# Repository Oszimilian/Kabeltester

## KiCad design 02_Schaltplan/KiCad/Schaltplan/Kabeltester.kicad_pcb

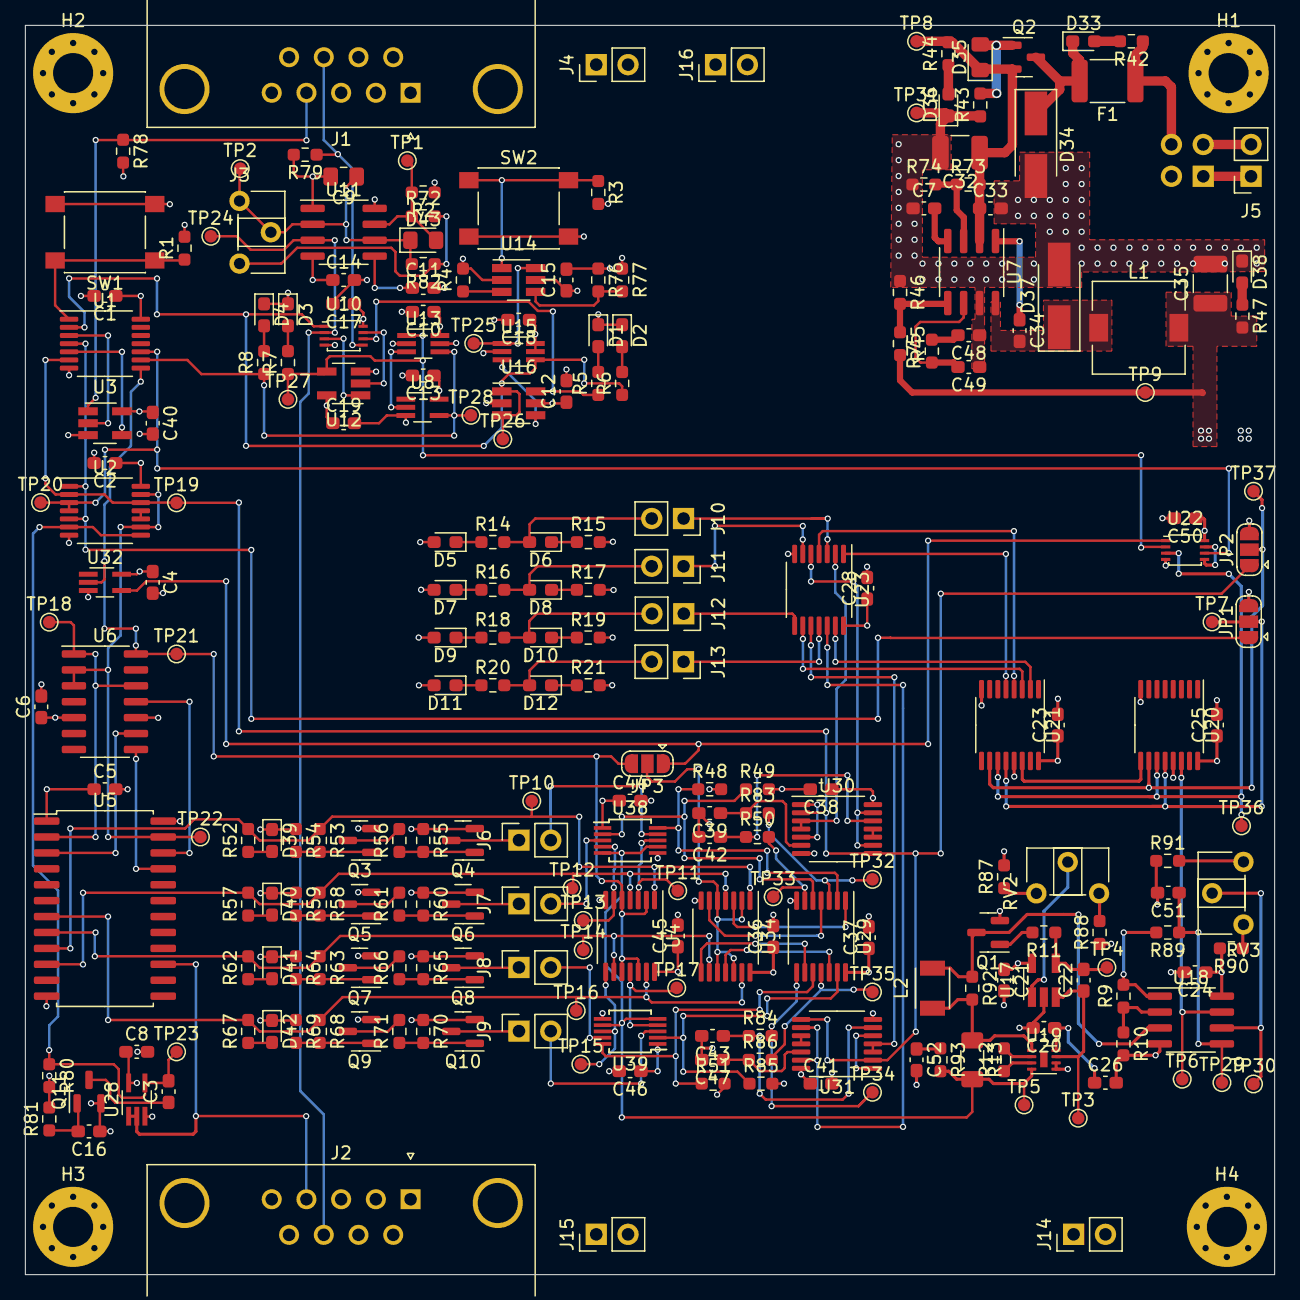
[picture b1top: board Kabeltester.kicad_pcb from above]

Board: 4 copper layers, 99.7 x 99.7 mm, 253 parts (1 on the bottom side), 160 nets.

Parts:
C1, C2, C3, C4, C5, C6, C8, C10, C11, C12, C13, C14, C15, C17, C18, C19, C20, C21, C23, C24, C25, C26, C28, C34, C36, C37, C38, C40, C41, C44, C45, C46, C50, C51: 100nF; C_0603_1608Metric_Pad1.08x0.95mm_HandSolder
C7: 10pF; C_0603_1608Metric_Pad1.08x0.95mm_HandSolder
C9: 3,9uF; C_0805_2012Metric_Pad1.18x1.45mm_HandSolder
C16: 1uF; C_0603_1608Metric_Pad1.08x0.95mm_HandSolder
C22: 1nF; C_0603_1608Metric_Pad1.08x0.95mm_HandSolder
C32: 22uF; C_1210_3225Metric_Pad1.33x2.70mm_HandSolder
C33, C52: 10nF; C_0603_1608Metric_Pad1.08x0.95mm_HandSolder
C35: 100uF; C_1210_3225Metric_Pad1.33x2.70mm_HandSolder
C39, C42, C43, C47: 470nF; C_0603_1608Metric_Pad1.08x0.95mm_HandSolder
C48: 2nF; C_0603_1608Metric_Pad1.08x0.95mm_HandSolder
C49: 8,2nF; C_0603_1608Metric_Pad1.08x0.95mm_HandSolder
D1, D5, D7, D9, D11, D33: LED/ROT; LED_0603_1608Metric_Pad1.05x0.95mm_HandSolder
D2, D6, D8, D10, D12, D36, D38: LED/GRUEN; LED_0603_1608Metric_Pad1.05x0.95mm_HandSolder
D3, D4, D39, D40, D41, D42: LED/GELB; LED_0603_1608Metric_Pad1.05x0.95mm_HandSolder
D34: SMAJ10CA; D_SMA_Handsoldering
D35: BZX585-C5V1; D_0805_2012Metric_Pad1.15x1.40mm_HandSolder
D37: B340A; D_SMA_Handsoldering
D43: BAS416; D_0805_2012Metric_Pad1.15x1.40mm_HandSolder
F1: 100mA M; Fuse_1812_4532Metric_Pad1.30x3.40mm_HandSolder
H1, H2, H3, H4: MountingHole; MountingHole_3.2mm_M3_Pad_Via
J1: INPUT/MALE-DB9; DSUB-9_Male_Horizontal_P2.77x2.84mm_EdgePinOffset4.94mm_Hou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
J2: OUTPUT/FEMALE-DB9; DSUB-9_Female_Horizontal_P2.77x2.84mm_EdgePinOffset4.94mm_H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
J3: 5k Poti; Potentiometer_ACP_CA6-H2,5_Horizontal
J4: VCC; PinHeader_1x02_P2.54mm_Vertical
J5: 9V_Batt; PinSocket_1x02_P2.54mm_Vertical
J6, J7, J8, J9: MEASURE-CON; PinSocket_1x02_P2.54mm_Vertical
J10, J11, J12, J13: Conn_02x01; PinSocket_1x02_P2.54mm_Vertical
J14, J15, J16: GND; PinHeader_1x02_P2.54mm_Vertical
JP1, JP2, JP3: Jumper; SolderJumper-3_P1.3mm_Open_RoundedPad1.0x1.5mm
L1: 6,8uH; L_7.3x7.3_H4.5
L2: L; L_TDK_NLV32_3.2x2.5mm
Q1: SI2318; SOT-23
Q2, Q4, Q6, Q8, Q10: Si2301; SOT-23
Q3, Q5, Q7, Q9: BSS123; SOT-23
Q11: BC858; SOT-23
R1, R3, R43, R48, R49, R50, R51, R54, R55, R59, R60, R64, R65, R69, R70, R78, R79, R80, R81, R83, R84, R85, R86, R89: 10k; R_0603_1608Metric_Pad0.98x0.95mm_HandSolder
R2: 18k; R_0603_1608Metric_Pad0.98x0.95mm_HandSolder
R4: 820k; R_0603_1608Metric_Pad0.98x0.95mm_HandSolder
R5, R7, R8, R14, R16, R18, R20, R52, R57, R62, R67: 1k6; R_0603_1608Metric_Pad0.98x0.95mm_HandSolder
R6, R15, R17, R19, R21, R47: 1k2; R_0603_1608Metric_Pad0.98x0.95mm_HandSolder
R9, R56, R61, R66, R71, R90, R91: 0R; R_0603_1608Metric_Pad0.98x0.95mm_HandSolder
R10, R82: NP; R_0603_1608Metric_Pad0.98x0.95mm_HandSolder
R11: 1k8; R_0603_1608Metric_Pad0.98x0.95mm_HandSolder
R12, R87, R88: 1k; R_0603_1608Metric_Pad0.98x0.95mm_HandSolder
R13: 1R; R_1206_3216Metric_Pad1.30x1.75mm_HandSolder
R42: 3k9; R_0603_1608Metric_Pad0.98x0.95mm_HandSolder
R44: 3k3; R_0603_1608Metric_Pad0.98x0.95mm_HandSolder
R45: 10k2; R_0603_1608Metric_Pad0.98x0.95mm_HandSolder
R46: 1k96; R_0603_1608Metric_Pad0.98x0.95mm_HandSolder
R53, R58, R63, R68: 510R; R_0603_1608Metric_Pad0.98x0.95mm_HandSolder
R72: 15k; R_0603_1608Metric_Pad0.98x0.95mm_HandSolder
R73: 680k; R_0603_1608Metric_Pad0.98x0.95mm_HandSolder
R74: 150k; R_0603_1608Metric_Pad0.98x0.95mm_HandSolder
R75: 34k; R_0603_1608Metric_Pad0.98x0.95mm_HandSolder
R76: 560k; R_0603_1608Metric_Pad0.98x0.95mm_HandSolder
R77: 1M; R_0603_1608Metric_Pad0.98x0.95mm_HandSolder
R92: 22R; R_0603_1608Metric_Pad0.98x0.95mm_HandSolder
R93: ?; R_0603_1608Metric_Pad0.98x0.95mm_HandSolder
RV2, RV3: 20k; Potentiometer_ACP_CA6-H2,5_Horizontal
SW1: START; SW_Push_1P1T_NO_6x6mm_H9.5mm
SW2: MODE; SW_Push_1P1T_NO_6x6mm_H9.5mm
SW3: PWR ON/OFF; PinSocket_2x02_P2.54mm_Vertical
TP1, TP2, TP3, TP4, TP5, TP6, TP7, TP8, TP9, TP10, TP11, TP12, TP13, TP14, TP15, TP16, TP17, TP18, TP19, TP20, TP21, TP22, TP23, TP24, TP25, TP26, TP27, TP28, TP29, TP30, TP31, TP32, TP33, TP34, TP35, TP36, TP37: TestPoint; TestPoint_Pad_D1.0mm
U1, U4, U23, U34: 74HC08PW; TSSOP-14_4.4x5mm_P0.65mm
U2, U30, U31: 74HC02PW; TSSOP-14_4.4x5mm_P0.65mm
U3, U12: 74AHC1G32; SOT-23-5_HandSoldering
U5: CD74HC4514M96; SOIC-24W_7.5x15.4mm_P1.27mm
U6: SN74LS93; SOIC-14_3.9x8.7mm_P1.27mm
U7: TPS_54331; SOIC-8_3.9x4.9mm_P1.27mm
U8, U32: 74AHC1G14; SOT-353_SC-70-5_Handsoldering
U10, U22: 74AHC2G08; VSSOP-8_2.4x2.1mm_P0.5mm
U11: NE555; SOIC-8_3.9x4.9mm_P1.27mm
U13, U15: 74LVC1G175; SOT-363_SC-70-6_Handsoldering
U14: LTC6993; SOT-23-6_Handsoldering
U16: 74LVC2G14; SOT-23-6_Handsoldering
U17: LMV321AUIDBVR; SOT-23-5_HandSoldering
U18: LMV358MM; SOIC-8_3.9x4.9mm_P1.27mm
U19: INA826AIDRGT; DFN-8-1EP_2x2mm_P0.5mm_EP0.6x1.2mm
U20, U21: 74HC595; TSSOP-16_4.4x5mm_P0.65mm
U28: 74HC1G126; SOT-353_SC-70-5_Handsoldering
U29: 74HC86PW; TSSOP-14_4.4x5mm_P0.65mm
U38, U39: DG2535; MSOP-10_3x3mm_P0.5mm

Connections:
+5V: C1.1, C2.1, C4.1, C5.1, C6.1, C8.1, C10.1, C12.1, C13.1, C14.1, C15.1, C16.1, C17.1, C18.1, C19.1, C20.1, C21.1, C23.1, C24.1, C25.1, C26.1, C28.1, C35.1, C36.1, C37.1, C38.1, C40.1, C41.1, C44.1, C45.1, C46.1, C50.1, D5.2 (A), D7.2 (A), D9.2 (A), D11.2 (A), J1.1, J1.5, J2.1, J2.5, J4.1, J4.2, JP1.3 (B), JP2.3 (B), L1.2, Q4.2 (S), Q6.2 (S), Q8.2 (S), Q10.2 (S), Q11.2 (E), R2.1, R45.2, R47.2, R55.1, R60.1, R65.1, R70.1, R77.1, R87.2, R90.2, SW1.2, SW2.2, TP9.1, U1.14 (VCC), U2.14 (VCC), U3.5 (VCC), U4.14 (VCC), U5.1 (LE), U5.24 (VCC), U6.5 (VCC), U8.5 (VCC), U10.8 (VCC), U11.4 (RESET), U11.8 (VCC), U12.5 (VCC), U13.5 (VCC), U13.6 (MR), U14.5 (VCC), U15.5 (VCC), U15.6 (MR), U16.5 (VCC), U17.5 (V+), U18.8 (V+), U19.8 (+VS), U20.16 (VCC), U21.16 (VCC), U22.8 (VCC), U23.14 (VCC), U28.5 (VCC), U29.14 (VCC), U30.14 (VCC), U31.14 (VCC), U32.5 (VCC), U34.14 (VCC), U38.1 (V+), U39.1 (V+)
+9V: C32.1, C33.1, D35.1 (K), Q2.2 (S), R44.2, R73.2, TP8.1, U7.2 (VIN)
/Versorgung/PH: C34.2, D37.1 (K), L1.1, U7.8 (PH)
CC_Output: TP6.1, U18.7, U20.14 (SER)
CC_Voltage: L2.2, Q1.3 (D), R92.1, U18.3 (+)
DK_INPUT_1: R48.1, U29.2 (1B), U38.10 (NO2)
DK_INPUT_2: R49.1, U29.5 (2B), U38.2 (NO1)
DK_INPUT_3: R51.1, U29.10 (3B), U39.10 (NO2)
DK_INPUT_4: R85.1, U29.13 (4B), U39.2 (NO1)
DK_OUT_1: U23.2 (B), U30.3 (1B), U30.4 (2Y)
DK_OUT_2: U23.5 (B), U30.9 (3B), U30.13 (4Y)
DK_OUT_3: U23.10 (B), U31.3 (1B), U31.4 (2Y)
DK_OUT_4: U23.12 (B), U31.9 (3B), U31.13 (4Y)
GND: C1.2, C2.2, C4.2, C5.2, C6.2, C7.1, C8.2, C9.2, C10.2, C11.2, C12.2, C13.2, C14.2, C15.2, C17.2, C18.2, C19.2, C20.2, C21.2, C23.2, C24.2, C25.2, C26.2, C28.2, C32.2, C33.2, C35.2, C36.2, C37.2, C38.2, C39.2, C40.2, C41.2, C42.2, C43.2, C44.2, C45.2, C46.2, C47.2, C48.1, C49.1, C50.2, C51.2, C52.2, D1.1 (K), D2.1 (K), D3.1 (K), D4.1 (K), D34.2 (A2), D36.1 (K), D37.2 (A), D38.1 (K), D39.1 (K), D40.1 (K), D41.1 (K), D42.1 (K), J1.6, J1.9, J2.6, J2.9, J14.1, J14.2, J15.1, J15.2, J16.1, J16.2, Q1.2 (S), Q3.2 (S), Q5.2 (S), Q7.2 (S), Q9.2 (S), R1.2, R3.2, R4.2, R10.2, R15.2, R17.2, R19.2, R21.2, R43.1, R46.1, R48.2, R49.2, R51.2, R54.1, R59.1, R64.1, R69.1, R74.1, R76.1, R78.2, R79.2, R80.2, R81.2, R85.2, R88.1, R91.1, SW3.2, TP31.1, U1.7 (GND), U2.7 (GND), U3.3 (GND), U4.7 (GND), U5.12 (GND), U6.10 (GND), U7.7 (GND), U8.3 (GND), U10.4 (GND), U11.1 (GND), U12.3 (GND), U13.2 (GND), U14.2 (GND), U15.2 (GND), U16.2 (GND), U17.2 (V-), U18.4 (V-), U19.5 (+VS), U19.6 (Ref), U20.8 (GND), U20.13 (EN), U21.8 (GND), U21.13 (EN), U22.4 (GND), U23.7 (GND), U28.3 (GND), U29.7 (GND), U30.7 (GND), U31.7 (GND), U32.3 (GND), U34.7 (GND), U38.6 (GND), U39.6 (GND)
INPUT_MEASURE_GOON: J1.4, R78.1, U3.1 (1A)
KS_INPUT: R13.2, R93.2, TP5.1, U19.4 (V+), U38.5 (NC1), U38.7 (NC2), U39.5 (NC1), U39.7 (NC2)
KS_OUT_1: U21.5 (QF), U23.1 (A)
KS_OUT_2: U21.4 (QE), U23.4 (A)
KS_OUT_3: U21.3 (QD), U23.9 (A)
KS_OUT_4: U21.2 (QC), U23.13 (A)
MEASURE_START: U1.5 (B), U3.4 (1Y)
NE55_OUT: J2.8, TP24.1, U10.2 (1B), U11.3 (OUT)
unnamed: C3.1, Q11.3 (C)
unnamed: C7.2, U7.4 (SS)
unnamed: C9.1, D43.1 (K), J3.1, J3.2, R82.2, TP2.1, U11.2 (TRIG), U11.6 (THRES)
unnamed: C11.1, U11.5 (CONT)
unnamed: C16.2, Q11.1 (B), R81.1
unnamed: C22.1, TP3.1, U17.3 (-)
unnamed: C22.2, R11.1, TP4.1, U17.4
unnamed: C34.1, U7.1 (BOOT)
unnamed: C39.1, R83.1, U30.6 (2B)
unnamed: C42.1, R50.1, U30.12 (4B)
unnamed: C43.1, R84.1, U31.6 (2B)
unnamed: C47.1, R86.1, U31.12 (4B)
unnamed: C48.2, R75.2
unnamed: C49.2, R75.1, U7.6 (COMP)
unnamed: C51.1, R89.1, TP29.1, U18.5 (+)
unnamed: C52.1, R93.1
unnamed: D1.2 (A), R5.2
unnamed: D2.2 (A), R6.2
unnamed: D3.2 (A), R7.2
unnamed: D4.2 (A), R8.2
unnamed: D5.1 (K), R14.1
unnamed: D6.1 (K), R15.1
unnamed: D6.2 (A), J10.2, R14.2
unnamed: D7.1 (K), R16.1
unnamed: D8.1 (K), R17.1
unnamed: D8.2 (A), J11.2, R16.2
unnamed: D9.1 (K), R18.1
unnamed: D10.1 (K), R19.1
unnamed: D10.2 (A), J12.2, R18.2
unnamed: D11.1 (K), R20.1
unnamed: D12.1 (K), R21.1
unnamed: D12.2 (A), J13.2, R20.2
unnamed: D33.1 (K), D34.1 (A1), F1.2, Q2.3 (D)
unnamed: D33.2 (A), R42.2
unnamed: D35.2 (A), Q2.1 (G), R43.2
unnamed: D36.2 (A), R44.1
unnamed: D38.2 (A), R47.1
unnamed: D39.2 (A), R52.1
unnamed: D40.2 (A), R57.1
unnamed: D41.2 (A), R62.1
unnamed: D42.2 (A), R67.1
unnamed: D43.2 (A), R2.2, R72.1, TP1.1, U11.7 (DISCH)
unnamed: F1.1, R42.1, SW3.4
unnamed: J3.3, R72.2, R82.1
unnamed: J5.1, SW3.1
unnamed: J5.2, SW3.3
unnamed: J6.1, Q4.3 (D)
unnamed: J6.2, U38.9 (COM2)
unnamed: J7.1, Q6.3 (D)
unnamed: J7.2, U38.3 (COM1)
unnamed: J8.1, Q8.3 (D)
unnamed: J8.2, U39.9 (COM2)
unnamed: J9.1, Q10.3 (D)
unnamed: J9.2, U39.3 (COM1)
unnamed: J10.1, U23.3 (Q)
unnamed: J11.1, U23.6 (Q)
unnamed: J12.1, U23.8 (Q)
unnamed: J13.1, U23.11 (Q)
unnamed: JP1.2 (C), TP7.1, U20.12 (RCK), U21.12 (RCK)
unnamed: JP2.2 (C), TP37.1, U20.10 (SRCLR), U21.10 (SRCLR)
unnamed: Q1.1 (G), R11.2
unnamed: Q3.1 (G), R53.2, R54.2
unnamed: Q3.3 (D), R56.2
unnamed: Q4.1 (G), R55.2, R56.1
unnamed: Q5.1 (G), R58.2, R59.2
unnamed: Q5.3 (D), R61.2
unnamed: Q6.1 (G), R60.2, R61.1
unnamed: Q7.1 (G), R63.2, R64.2
unnamed: Q7.3 (D), R66.2
unnamed: Q8.1 (G), R65.2, R66.1
unnamed: Q9.1 (G), R68.2, R69.2
unnamed: Q9.3 (D), R71.2
unnamed: Q10.1 (G), R70.2, R71.1
unnamed: R1.1, SW1.1, U1.1 (A)
unnamed: R3.1, SW2.1, U14.1 (TRIG)
unnamed: R4.1, U14.3 (SET)
unnamed: R5.1, U10.6 (2B), U16.6
unnamed: R9.1, R10.1, U18.2 (-)
unnamed: R12.1, U19.3 (G)
unnamed: R12.2, U19.2 (G)
unnamed: R13.1, R92.2, U19.1 (V-)
unnamed: R45.1, R46.2, U7.5 (VSENS)
unnamed: R50.2, TP33.1, U29.6 (2Y)
unnamed: R73.1, R74.2, U7.3 (EN)
unnamed: R76.2, R77.2, U14.4 (DIV)
unnamed: R83.2, TP32.1, U29.3 (1Y)
unnamed: R84.2, TP34.1, U29.8 (3Y)
unnamed: R86.2, TP35.1, U29.11 (4Y)
unnamed: R87.1, RV2.1
unnamed: R88.2, RV2.3
unnamed: R9.2, R89.2, U18.1
unnamed: R90.1, RV3.1
unnamed: R91.2, RV3.3
unnamed: RV2.2, U17.1 (+)
unnamed: RV3.2, TP30.1, U18.6 (-)
unnamed: TP11.1, U4.3 (Q), U38.8 (IN2)
unnamed: TP13.1, U4.6 (Q), U38.4 (IN1)
unnamed: TP15.1, U4.8 (Q), U39.8 (IN2)
unnamed: TP17.1, U4.11 (Q), U39.4 (IN1)
unnamed: TP18.1, U5.2 (A0), U6.1 (CKB), U6.12 (QA)
unnamed: TP25.1, U14.6 (OUT), U15.1 (CP)
unnamed: TP36.1, U20.11 (SRCK), U21.11 (SRCK), U22.3 (1Y)
unnamed: U1.3 (Q), U3.2 (1B)
unnamed: U2.10 (3Y), U2.11 (4A)
unnamed: U5.3 (A1), U6.9 (QB)
unnamed: U5.21 (A2), U6.8 (QC)
unnamed: U5.22 (A3), U6.11 (QD)
unnamed: U10.3 (1Y), U12.1 (1A)
unnamed: U10.7 (1Y), U12.2 (1B)
unnamed: U8.4, U13.3 (D)
unnamed: U15.3 (D), U16.4
unnamed: U20.9 (QS), U21.14 (SER)
unnamed: U22.5 (2A), U22.7 (1Y)
unnamed: U29.1 (1A), U34.3 (Q)
unnamed: U29.4 (2A), U34.6 (Q)
unnamed: U29.9 (3A), U34.8 (Q)
unnamed: U29.12 (4A), U34.11 (Q)
unnamed: U30.1 (1Y), U30.5 (2A)
unnamed: U30.10 (3Y), U30.11 (4A)
unnamed: U31.1 (1Y), U31.5 (2A)
unnamed: U31.10 (3Y), U31.11 (4A)
OUTPUT_1: R52.2, R53.1, TP10.1, U4.1 (A), U5.9 (Y1), U34.1 (A)
OUTPUT_2: R57.2, R58.1, TP12.1, U4.4 (A), U5.10 (Y2), U34.4 (A)
OUTPUT_3: R62.2, R63.1, TP14.1, U4.9 (A), U5.8 (Y3), U34.9 (A)
OUTPUT_4: R67.2, R68.1, TP16.1, U4.13 (A), U5.7 (Y4), U34.13 (A)
OUTPUT_MEASURE_GOON: J2.4, U5.15 (Y15), U28.1, U28.2
OUT_RST_DEZ: TP22.1, U2.9 (3B), U2.13 (4Y), U5.23 (E), U6.2 (R1), U6.3 (R2)
RESET: JP2.1 (A), TP19.1, U1.6 (Q), U2.2 (1A), U2.12 (4B), U30.2 (1A), U30.8 (3A), U31.2 (1A), U31.8 (3A)
RST_DEZ: C3.2, R80.1, TP23.1, U2.6 (2B), U2.8 (3A), U28.4
SYSTEM_STATUS_SR: TP20.1, U1.10 (B), U2.3 (1B), U2.4 (2Y), U22.6 (2B)
SYSTEM_STATUS_SR_INV: JP1.1 (A), U1.4 (A), U2.1 (1Y), U2.5 (2A)
SYSTEM_TACK: R8.1, TP28.1, U1.9 (A), U8.2, U13.4 (Q)
SYSTEM_TACKT_SR: JP3.3 (B), TP21.1, U1.8 (Q), U4.2 (B), U4.5 (B), U4.10 (B), U4.12 (B), U6.14 (CKA), U32.2
SYSTEM_TACKT_SR_INV: JP3.1 (A), U22.1 (1A), U32.4
SYSTEM_TACKT_SR_INV1: JP3.2 (C), U34.2 (B), U34.5 (B), U34.10 (B), U34.12 (B)
SYSTEM_TACK_2: R7.1, TP27.1, U12.4 (1Y), U13.1 (CP)
TAKT_EXTERN: J1.8, R79.1, U10.5 (2A)
Tastensperre: R6.1, TP26.1, U1.2 (B), U10.1 (1A), U15.4 (Q), U16.1, U16.3

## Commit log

2021-04-08 Upload
    Schaltplan und Libery KiCad
2021-04-08 Upload
    Weitere Sachen einfach
2021-04-08 Upload
    Weitere Sachen
2021-04-08 Changes
    keine Änderungen
2021-04-10 ADD
    no Changes
    only automaticly backups
2021-04-12 ADD
    -Dokumentation erweitert
    -Schaltplan Fußbeschriftungen
2021-04-13 Changes & ADD
    +Bestückungsplan
    +Auftragsplannung
    @ Klärung verschiedener Begrifflichkeiten
2021-04-13 Change
    keine Beschreibung der Herangehensweiße
    vllt einfach Graphisch beschreiben
2021-04-14 BA_Blockschaltbild.drawio aktualisiert
2021-04-14 ADD
    Changes and ADD's
2021-04-14 Change
2021-04-16 Changes
    constant-current
2021-04-24 Changes
    Sheet Layout
2021-04-25 ADD & Changes
    Inbetriebnahme Tex
2021-04-26 Inbetriebnahme 'Doc
2021-04-26 Changes
    Delite CC-Logic-simulation-models
    Add-Folder Konstantstromquelle
2021-04-27 Changes
    Ordern-Struktur wurde geändert
    Inbetriebnahme wurde geändert
    USW.
2021-04-28 No Changes
2021-04-29 Backs
2021-04-29 Doku
    Schaltplan
    -Versorgung
    -Taktgeber
2021-05-01 Verbesserung
2021-05-02 Docu
2021-05-02 Änderungen
2021-05-03 nothing special
2021-05-07 ddd
    ADD's
    Changes
2021-05-13 ADD
    Weil PDF davor nicht vollständig
2021-05-14 Pflichtenheft
2021-05-20 Final Change
2021-05-21 Changes Final
2021-05-27 Nicht wichtig
2021-05-28 Nix wichtiges
